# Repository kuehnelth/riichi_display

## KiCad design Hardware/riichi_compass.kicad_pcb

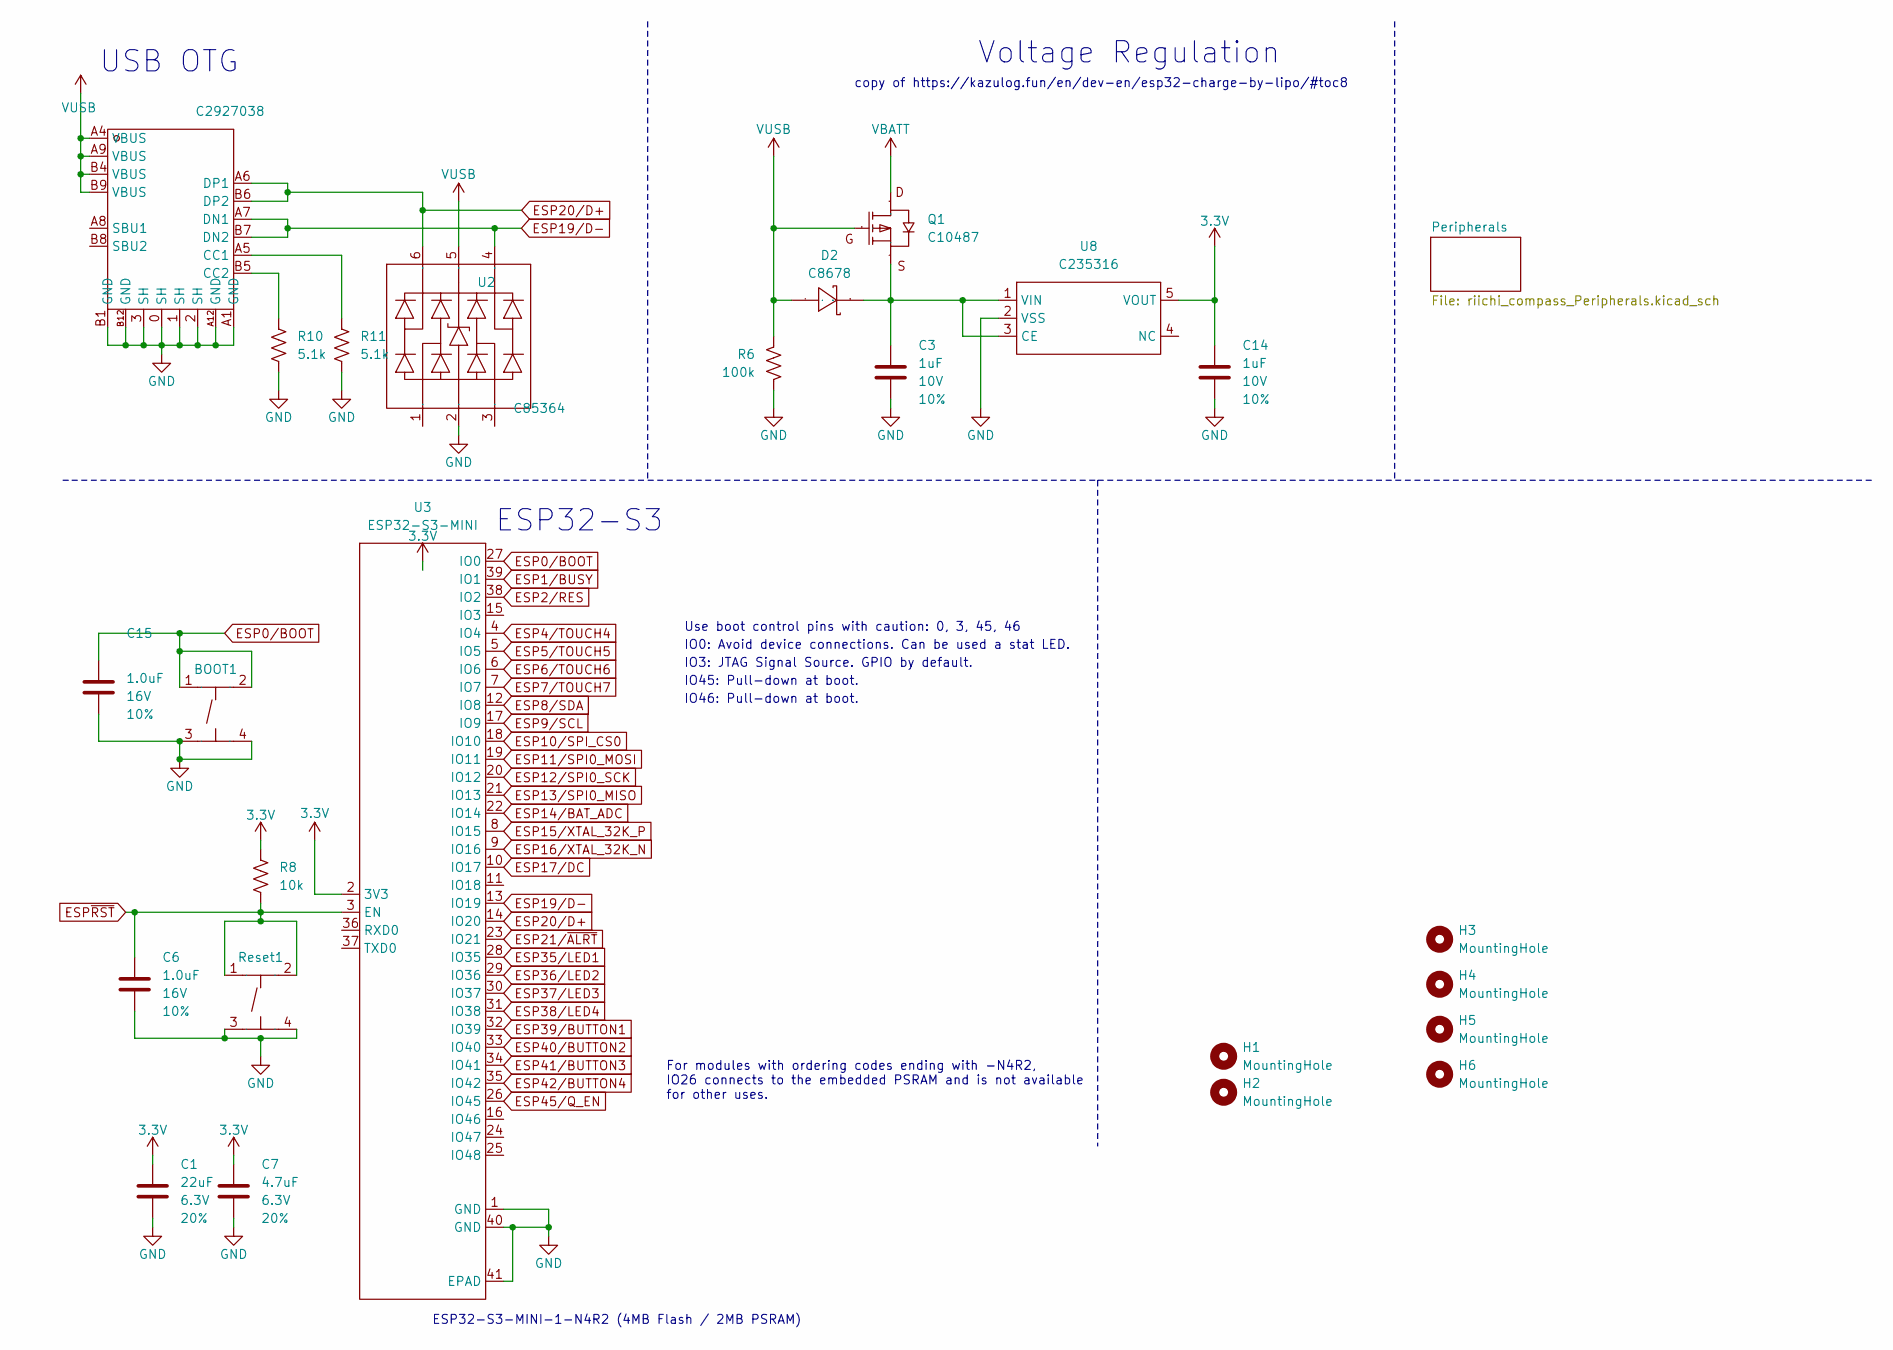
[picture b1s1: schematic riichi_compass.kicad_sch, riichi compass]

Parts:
BOOT1: C318884; SW-SMD_4P-L5.1-W5.1-P3.70-LS6.5-TL_H1.5; Manufacturer Part TS-1187A-B-A-B; LCSC Part Name 5.1*5.1*1.5mm 立贴 轻触开关
C1: 22uF; C_0603_1608Metric; Voltage 6.3V; Tolerance 20%
C3, C14: 1uF; C_0402_1005Metric; Voltage 10V; Tolerance 10%
C6, C15: 1.0uF; C_0402_1005Metric; Voltage 16V; Tolerance 10%
C7: 4.7uF; C_0402_1005Metric; Voltage 6.3V; Tolerance 20%
D2: C8678; SMA_L4.3-W2.6-LS5.2-RD; Manufacturer Part SS34; LCSC Part Name 电压:40V 电流:3A
H1, H2: MountingHole; MountingHole_6.4mm_M6_DIN965
H3, H4, H5, H6: MountingHole; MountingHole_2.7mm_M2.5_ISO14580
Q1: C10487; SOT-23-3_L3.0-W1.7-P0.95-LS2.9-BR; Manufacturer Part SI2301CDS-T1-GE3; LCSC Part Name 1个P沟道 耐压:20V 电流:3.1A
R6: 100k; R_0402_1005Metric
R8: 10k; R_0402_1005Metric
R10, R11: 5.1k; R_0402_1005Metric
Reset1: C318884; SW-SMD_4P-L5.1-W5.1-P3.70-LS6.5-TL_H1.5; Manufacturer Part TS-1187A-B-A-B; LCSC Part Name 5.1*5.1*1.5mm 立贴 轻触开关
U2: C85364; SOT-23-6_L2.9-W1.6-P0.95-LS2.9-BL; Manufacturer Part C85364; LCSC Part Name 丝印:V05 单向ESD 5V截止 峰值浪涌电流：4A@8/20us
U3: ESP32-S3-MINI; WIRELM-SMD_ESP32-S3-WROOM-1; Manufacturer Part ESP32-S3-WROOM-1; LCSC Part Name ESP32-S3-WROOM-1
U8: C235316; SOT-353_L2.1-W1.3-P0.65-LS2.3-BL; Manufacturer Part ME6211C33R5G; LCSC Part Name 输入6.5V 输出3.3V 300mA
USB2: C2927038; USB-C_SMD-TYPE-C-31-M-12; Manufacturer Part USB-TYPE-C-018; LCSC Part Name Type-C 母 卧贴

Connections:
3.3V: C1.2, C7.1, C14.1, R8.1, U3.2 (3V3), U8.5 (VOUT); also elsewhere on the board
ESP0/BOOT: BOOT1.1 (A), BOOT1.2 (B), C15.1, U3.27 (IO0)
ESP1/BUSY: U3.39 (IO1); also elsewhere on the board
ESP2/RES: U3.38 (IO2); also elsewhere on the board
ESP4/TOUCH4: U3.4 (IO4); also elsewhere on the board
ESP5/TOUCH5: U3.5 (IO5); also elsewhere on the board
ESP6/TOUCH6: U3.6 (IO6); also elsewhere on the board
ESP7/TOUCH7: U3.7 (IO7); also elsewhere on the board
ESP8/SDA: U3.12 (IO8); also elsewhere on the board
ESP9/SCL: U3.17 (IO9); also elsewhere on the board
ESP10/SPI_CS0: U3.18 (IO10); also elsewhere on the board
ESP11/SPI0_MOSI: U3.19 (IO11); also elsewhere on the board
ESP12/SPI0_SCK: U3.20 (IO12); also elsewhere on the board
ESP13/SPI0_MISO: U3.21 (IO13)
ESP14/BAT_ADC: U3.22 (IO14); also elsewhere on the board
ESP15/XTAL_32K_P: U3.8 (IO15); also elsewhere on the board
ESP16/XTAL_32K_N: U3.9 (IO16); also elsewhere on the board
ESP17/DC: U3.10 (IO17); also elsewhere on the board
ESP19/D-: U2.4 (I/O), U3.13 (IO19), USB2.A7 (DN1), USB2.B7 (DN2)
ESP20/D+: U2.6 (I/O), U3.14 (IO20), USB2.A6 (DP1), USB2.B6 (DP2)
ESP21/~ALRT: U3.23 (IO21); also elsewhere on the board
ESP35/LED1: U3.28 (IO35); also elsewhere on the board
ESP36/LED2: U3.29 (IO36); also elsewhere on the board
ESP37/LED3: U3.30 (IO37); also elsewhere on the board
ESP38/LED4: U3.31 (IO38); also elsewhere on the board
ESP39/BUTTON1: U3.32 (IO39); also elsewhere on the board
ESP40/BUTTON2: U3.33 (IO40); also elsewhere on the board
ESP41/BUTTON3: U3.34 (IO41); also elsewhere on the board
ESP42/BUTTON4: U3.35 (IO42); also elsewhere on the board
ESP45/Q_EN: U3.26 (IO45)
ESP~RST: C6.1, R8.2, Reset1.1 (A), Reset1.2 (B), U3.3 (EN)
GND: BOOT1.3 (C), BOOT1.4 (D), C1.1, C3.2, C6.2, C7.2, C14.2, C15.2, R6.2, R10.1, R11.2, Reset1.3 (C), Reset1.4 (D), U2.2 (VN), U3.1 (GND), U3.40 (GND), U3.41 (EPAD), U8.2 (VSS), USB2.0 (SH), USB2.1 (SH), USB2.2 (SH), USB2.3 (SH), USB2.A1 (GND), USB2.A12 (GND), USB2.B1 (GND), USB2.B12 (GND); also elsewhere on the board
unnamed: C3.1, D2.1 (K), Q1.2 (S), U8.1 (VIN), U8.3 (CE)
unnamed: R11.1, USB2.A5 (CC1)
unnamed: R10.2, USB2.B5 (CC2)
VBATT: Q1.3 (D); also elsewhere on the board
VUSB: D2.2 (A), Q1.1 (G), R6.1, U2.5 (VP), USB2.A4 (VBUS), USB2.A9 (VBUS), USB2.B4 (VBUS), USB2.B9 (VBUS); also elsewhere on the board

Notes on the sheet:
ESP32-S3
copy of https://kazulog.fun/en/dev-en/esp32-charge-by-lipo/#toc8
IO46: Pull-down at boot.
For modules with ordering codes ending with -N4R2, IO26 connects to the embedded PSRAM and is not available for other uses.
IO45: Pull-down at boot.
IO3: JTAG Signal Source. GPIO by default.
USB OTG
ESP32-S3-MINI-1-N4R2 (4MB Flash / 2MB PSRAM)
Voltage Regulation
IO0: Avoid device connections. Can be used a stat LED.
Use boot control pins with caution: 0, 3, 45, 46

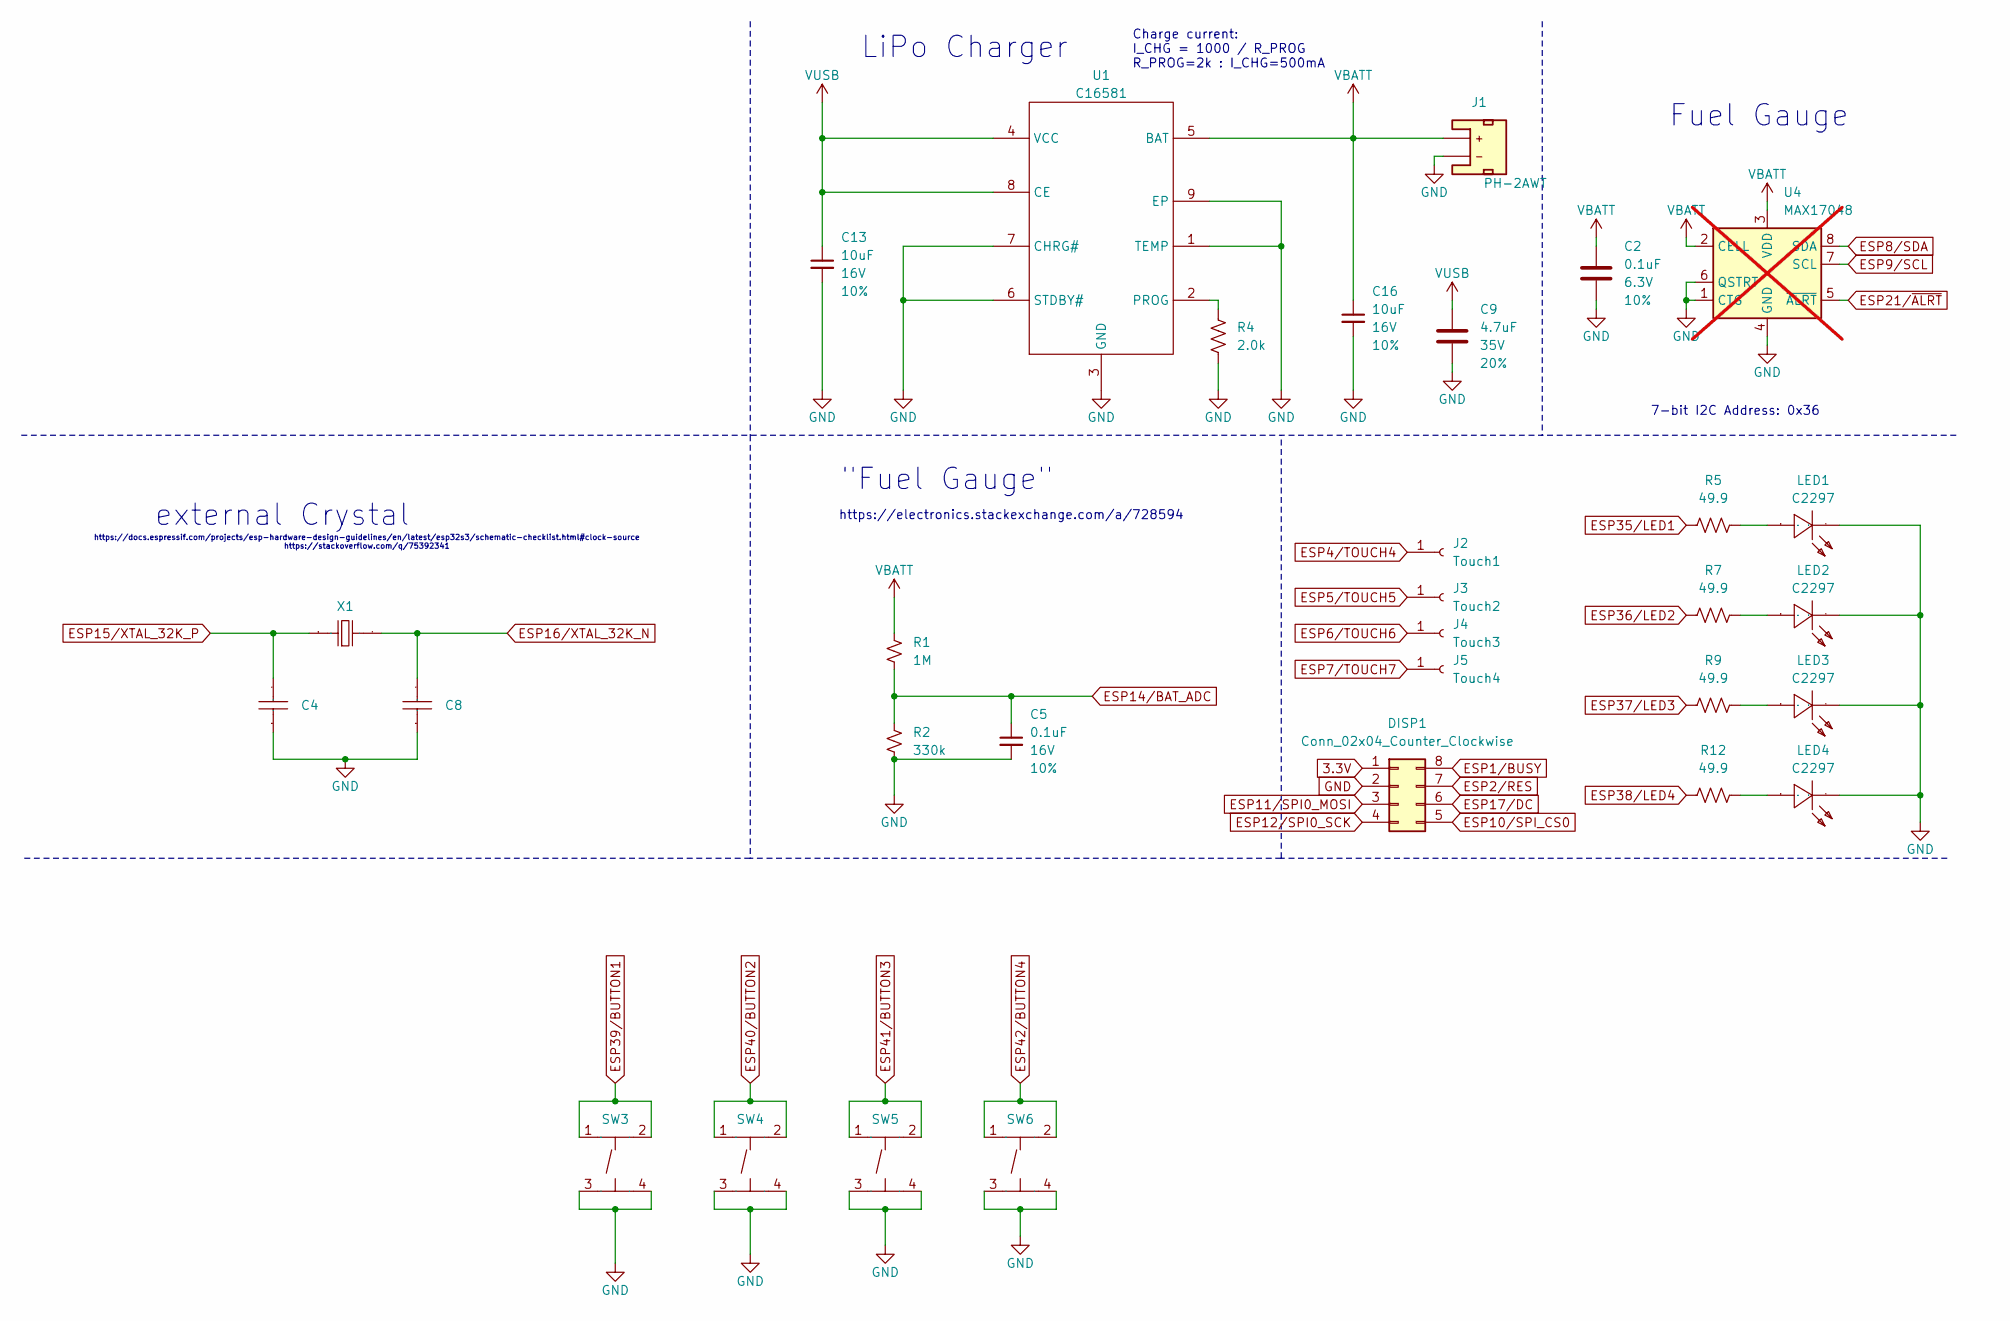
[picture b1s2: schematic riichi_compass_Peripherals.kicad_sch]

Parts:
C2: 0.1uF; C_0402_1005Metric; Voltage 6.3V; Tolerance 10%
C4, C8: 15pF; C0402; Manufacturer Part 0402CG4R0C500NT; LCSC Part Name ±0.25pF 4pF 50V
C5: 0.1uF; C_0402_1005Metric; Voltage 16V; Tolerance 10%
C9: 4.7uF; C_0402_1005Metric; Voltage 35V; Tolerance 20%
C13, C16: 10uF; C_0402_1005Metric; Voltage 16V; Tolerance 10%
DISP1: Conn_02x04_Counter_Clockwise; PinSocket_2x04_P2.54mm_Vertical
J1: PH-2AWT; CONN-SMD_PH-2AWT; JLC C2763693
J2: Touch1; PinSocket_1x01_P2.54mm_Horizontal
J3: Touch2; PinSocket_1x01_P2.54mm_Horizontal
J4: Touch3; PinSocket_1x01_P2.54mm_Horizontal
J5: Touch4; PinSocket_1x01_P2.54mm_Horizontal
LED1, LED2, LED3, LED4: C2297; LED0805-R-RD; Manufacturer Part KT-0805G; LCSC Part Name 0805 翠绿 高亮
R1: 1M; R_0603_1608Metric
R2: 330k; R_0603_1608Metric
R4: 2.0k; R_0402_1005Metric
R5, R7, R9, R12: 49.9; R_0402_1005Metric
SW3, SW4, SW5, SW6: C318884; SW-SMD_4P-L5.1-W5.1-P3.70-LS6.5-TL_H1.5; Manufacturer Part TS-1187A-B-A-B; LCSC Part Name 5.1*5.1*1.5mm 立贴 轻触开关
U1: C16581; ESOP-8_L4.9-W3.9-P1.27-LS6.0-BL-EP; Manufacturer Part TP4056-42-ESOP8; LCSC Part Name 单节锂离子电池线性充电器
U4: MAX17048; DFN-8; not fitted
X1: C32346; FC-135R_L3.2-W1.5; Manufacturer Part Q13FC13500004; LCSC Part Name 32.768kHz ±20ppm 12.5pF

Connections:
3.3V: DISP1.1; also elsewhere on the board
ESP1/BUSY: DISP1.8; also elsewhere on the board
ESP2/RES: DISP1.7; also elsewhere on the board
ESP4/TOUCH4: J2.1; also elsewhere on the board
ESP5/TOUCH5: J3.1; also elsewhere on the board
ESP6/TOUCH6: J4.1; also elsewhere on the board
ESP7/TOUCH7: J5.1; also elsewhere on the board
ESP8/SDA: U4.8 (SDA); also elsewhere on the board
ESP9/SCL: U4.7 (SCL); also elsewhere on the board
ESP10/SPI_CS0: DISP1.5; also elsewhere on the board
ESP11/SPI0_MOSI: DISP1.3; also elsewhere on the board
ESP12/SPI0_SCK: DISP1.4; also elsewhere on the board
ESP14/BAT_ADC: C5.1, R1.1, R2.2; also elsewhere on the board
ESP15/XTAL_32K_P: C4.2, X1.1; also elsewhere on the board
ESP16/XTAL_32K_N: C8.2, X1.2; also elsewhere on the board
ESP17/DC: DISP1.6; also elsewhere on the board
ESP21/~ALRT: U4.5 (~ALRT); also elsewhere on the board
ESP35/LED1: R5.1; also elsewhere on the board
ESP36/LED2: R7.1; also elsewhere on the board
ESP37/LED3: R9.1; also elsewhere on the board
ESP38/LED4: R12.1; also elsewhere on the board
ESP39/BUTTON1: SW3.1 (A), SW3.2 (B); also elsewhere on the board
ESP40/BUTTON2: SW4.1 (A), SW4.2 (B); also elsewhere on the board
ESP41/BUTTON3: SW5.1 (A), SW5.2 (B); also elsewhere on the board
ESP42/BUTTON4: SW6.1 (A), SW6.2 (B); also elsewhere on the board
GND: C2.2, C4.1, C5.2, C8.1, C9.2, C13.2, C16.2, DISP1.2, J1.1 (-), LED1.2 (K), LED2.2 (K), LED3.2 (K), LED4.2 (K), R2.1, R4.2, SW3.3 (C), SW3.4 (D), SW4.3 (C), SW4.4 (D), SW5.3 (C), SW5.4 (D), SW6.3 (C), SW6.4 (D), U1.1 (TEMP), U1.3 (GND), U1.6 (STDBY#), U1.7 (CHRG#), U1.9 (EP), U4.1 (CTG), U4.4 (GND), U4.6 (QSTRT), U4.9 (GND); also elsewhere on the board
unnamed: LED1.1 (A), R5.2
unnamed: LED2.1 (A), R7.2
unnamed: LED3.1 (A), R9.2
unnamed: LED4.1 (A), R12.2
unnamed: R4.1, U1.2 (PROG)
VBATT: C2.1, C16.1, J1.2 (+), R1.2, U1.5 (BAT), U4.2 (CELL), U4.3 (VDD); also elsewhere on the board
VUSB: C9.1, C13.1, U1.4 (VCC), U1.8 (CE); also elsewhere on the board

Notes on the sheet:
https://docs.espressif.com/projects/esp-hardware-design-guidelines/en/latest/esp32s3/schematic-checklist.html#clock-source https://stackoverflow.com/q/75392341
LiPo Charger
Charge current: I_CHG = 1000 / R_PROG R_PROG=2k : I_CHG=500mA
Fuel Gauge
external Crystal
https://electronics.stackexchange.com/a/728594
"Fuel Gauge"
7-bit I2C Address: 0x36

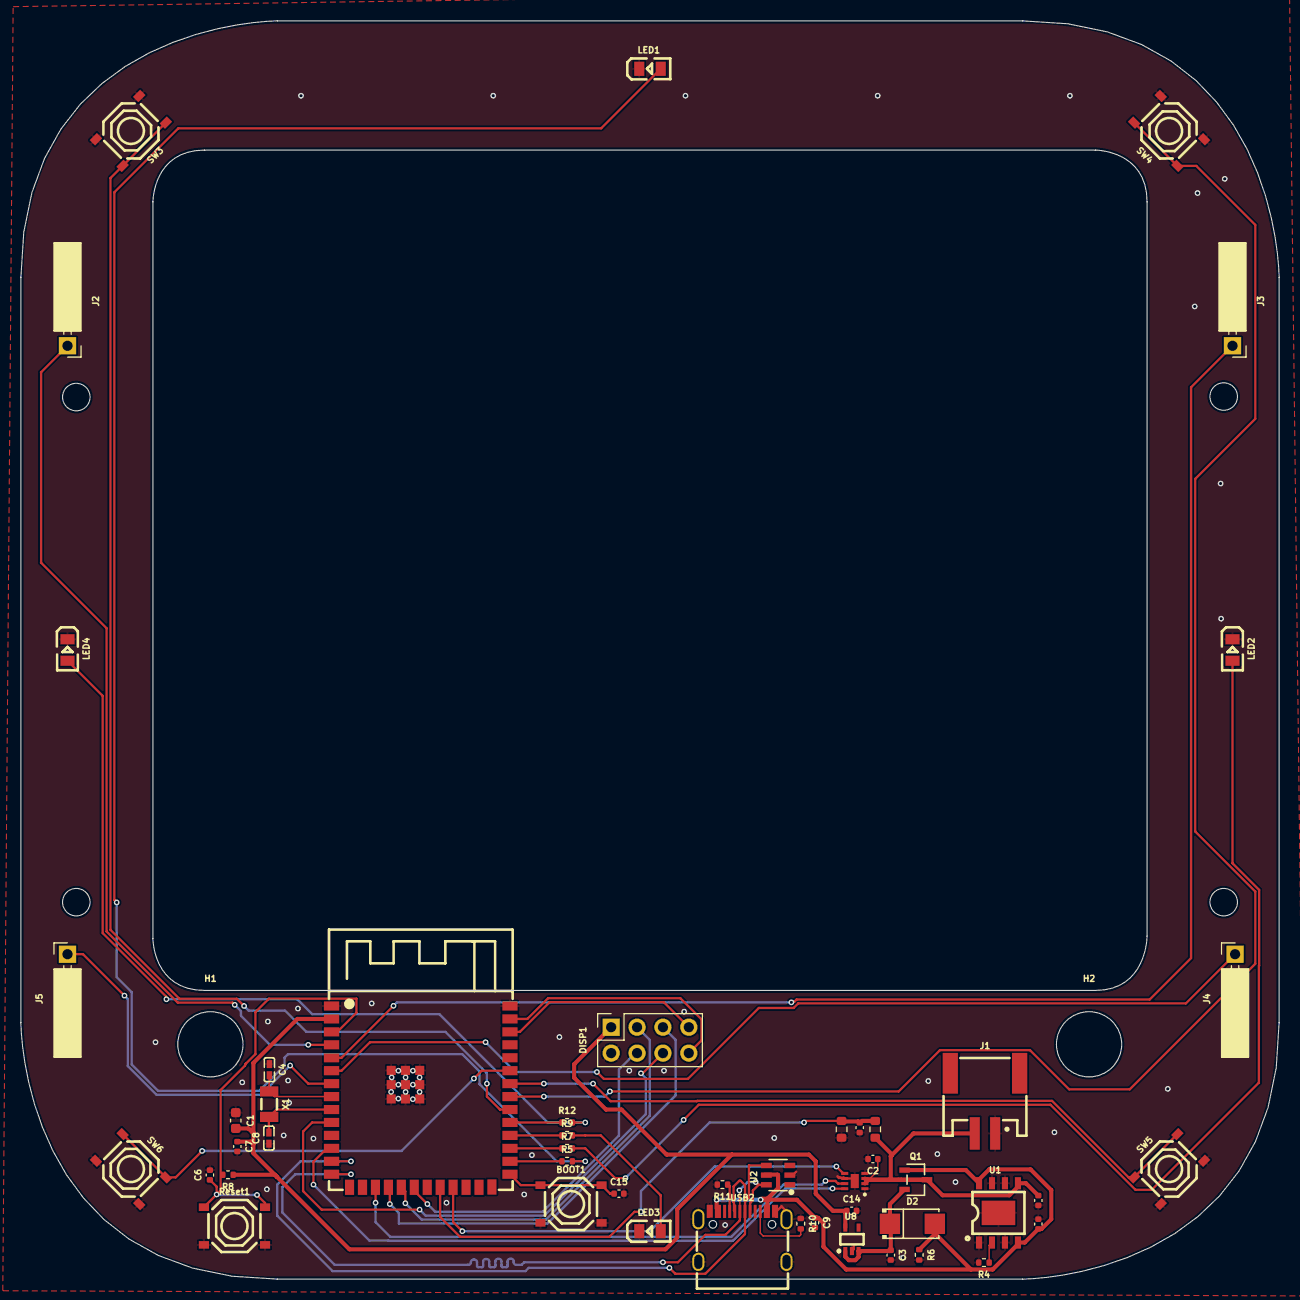
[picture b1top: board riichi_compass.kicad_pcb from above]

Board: 2 copper layers, 123.4 x 123.4 mm, 55 parts (0 on the bottom side), 40 nets.

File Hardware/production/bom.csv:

Designator,Footprint,Quantity,Value,LCSC Part #
"BOOT1, RESET1, SW3, SW4, SW5, SW6",SW-SMD_4P-L5.1-W5.1-P3.70-LS6.5-TL_H1.5,6,C318884,
C1,0603,1,22uF,
"C13, C16",0402,2,10uF,
"C14, C3",0402,2,1uF,
"C15, C6",0402,2,1.0uF,
"C2, C5",0402,2,0.1uF,
"C4, C8",C0402,2,15pF,
"C7, C9",0402,2,4.7uF,
D2,SMA_L4.3-W2.6-LS5.2-RD,1,C8678,
DISP1,PinSocket_2x04_P2.54mm_Vertical,1,Conn_02x04_Counter_Clockwise,
J1,CONN-SMD_PH-2AWT,1,PH-2AWT,C2763693
"LED1, LED2, LED3, LED4",LED0805-R-RD,4,C2297,
Q1,SOT-23-3_L3.0-W1.7-P0.95-LS2.9-BR,1,C10487,
R1,0603,1,1M,
"R10, R11",0402,2,5.1k,
"R12, R5, R7, R9",0402,4,49.9,
R2,0603,1,330k,
R4,0402,1,2.0k,
R6,0402,1,100k,
R8,0402,1,10k,
U1,ESOP-8_L4.9-W3.9-P1.27-LS6.0-BL-EP,1,C16581,
U2,SOT-23-6_L2.9-W1.6-P0.95-LS2.9-BL,1,C85364,
U8,SOT-353_L2.1-W1.3-P0.65-LS2.3-BL,1,C235316,
USB2,USB-C_SMD-TYPE-C-31-M-12,1,C2927038,
X1,FC-135R_L3.2-W1.5,1,C32346,

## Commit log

2025-08-20 init
2025-08-22 clang-format from kernel
2025-08-22 wider
2025-09-03 kinda works
2025-09-07 cleanup
2025-09-07 gitignore
2025-09-15 first kinda working prototype
2025-09-15 add fontconvert and m2 fonts
2025-11-02 initial change to riichi pcb
2025-11-05 funktioniert wahrscheinlich erst mal
2025-11-10 add link
2025-11-18 temp
2025-11-22 ignore zip
2025-11-22 update schematic (hopefully final)
2025-11-23 power part done
2025-11-29 1st production version
2025-11-29 remove generated stuff
2025-11-30 rename
2025-12-18 fix spi/serial
2025-12-23 fix buttons and leds
2025-12-23 custom sdkconfig
2025-12-23 add 3d model
2025-12-24 initial firmware commit
2025-12-24 add pio config
2025-12-24 init io
2025-12-24 initial BLE implementation
2025-12-24 add LED functions
2025-12-27 add game state and update from bt
2025-12-27 game_state: tabify
2025-12-27 io: no more camel case functions
2025-12-29 update GxEPD2 lib
2025-12-29 ble: add debug messages
2025-12-29 update active player in game state
2025-12-29 add need_redraw property to game state
2025-12-29 update main loop
2025-12-29 add display
2025-12-29 formatter configs
2025-12-29 update gitignore
